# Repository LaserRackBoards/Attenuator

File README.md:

# Attenuator
Voltage Controlled Attenuator based on Mini-Circuits RVA-3000

* BNC connector for control voltage
* SMA connectors for RF-in and RF-out
* 10-turn potentiometer for set-point

Used for laser power stabilization via control of AOM rf drive power.

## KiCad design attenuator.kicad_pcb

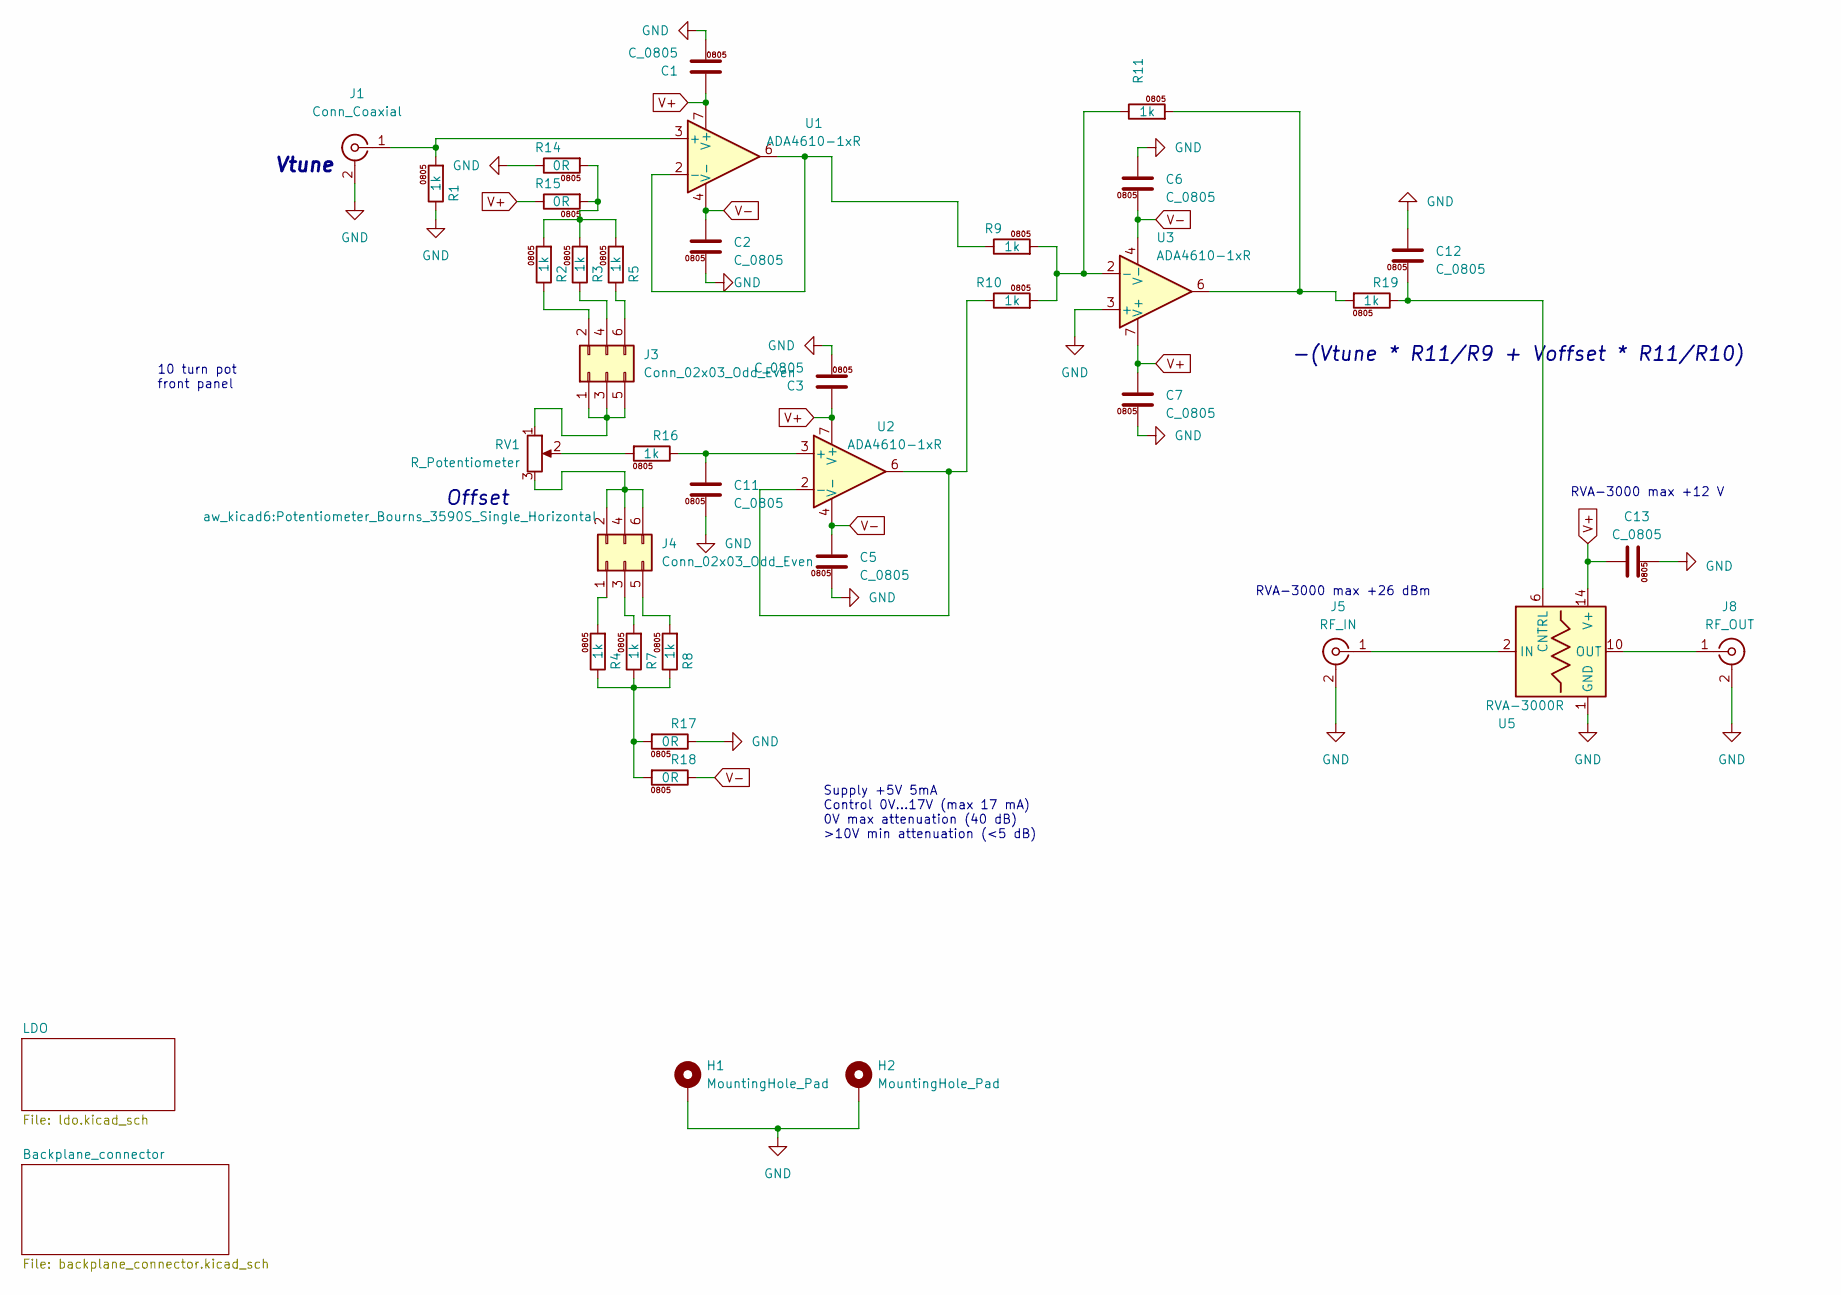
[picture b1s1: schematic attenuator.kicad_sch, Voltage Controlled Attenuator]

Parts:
C1, C2, C3, C5, C6, C7, C11, C12, C13: C_0805; C_0805_2012Metric
H1, H2: MountingHole_Pad; MountingHole_2.7mm_M2.5_DIN965_Pad
J1: Conn_Coaxial; BNC_Amphenol_B6252HB-NPP3G-50_Horizontal
J3, J4: Conn_02x03_Odd_Even; PinHeader_2x03_P2.54mm_Vertical
J5: RF_IN; SMA_Molex_73251-2200_Horizontal
J8: RF_OUT; SMA_Molex_73251-2200_Horizontal
R1, R2, R3, R4, R5, R7, R8, R9, R10, R11, R16, R19: 1k; R_0805_2012Metric
R14, R15, R17, R18: 0R; R_0805_2012Metric
RV1: R_Potentiometer; Potentiometer_Bourns_3590S_Single_Horizontal
U1, U2, U3: ADA4610-1xR; SOIC-8_3.9x4.9mm_P1.27mm
U5: RVA-3000R; Mini-Circuits_CK605

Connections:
GND: C1.2, C2.2, C3.2, C5.2, C6.1, C7.2, C11.2, C12.1, C13.2, H1.1, H2.1, J1.2 (Ext), J5.2 (Ext), J8.2 (Ext), R1.1, R14.1, R17.1, U3.3 (+), U5.1 (GND), U5.3 (GND), U5.4 (GND), U5.5 (GND), U5.7 (GND), U5.8 (GND), U5.9 (GND), U5.11 (GND), U5.12 (GND), U5.13 (GND), U5.15 (GND), U5.16 (GND); also elsewhere on the board
unnamed: J1.1 (In), R1.2, U1.3 (+)
unnamed: J3.1, J3.3, J3.5, RV1.1
unnamed: J3.2, R2.1
unnamed: J3.4, R3.1
unnamed: J3.6, R5.1
unnamed: J4.1, R4.2
unnamed: J4.2, J4.4, J4.6, RV1.3
unnamed: J4.3, R7.2
unnamed: J4.5, R8.2
unnamed: J5.1 (In), U5.2 (IN)
unnamed: J8.1 (In), U5.10 (OUT)
unnamed: R11.2, R19.2, U3.6
unnamed: R2.2, R3.2, R5.2, R14.2, R15.2
unnamed: R16.2, RV1.2
unnamed: R4.1, R7.1, R8.1, R17.2, R18.2
unnamed: R9.1, U1.2 (-), U1.6
unnamed: C11.1, R16.1, U2.3 (+)
unnamed: R10.1, U2.2 (-), U2.6
unnamed: R9.2, R10.2, R11.1, U3.2 (-)
unnamed: C12.2, R19.1, U5.6 (CNTRL)
V+: C1.1, C3.1, C7.1, C13.1, R15.1, U1.7 (V+), U2.7 (V+), U3.7 (V+), U5.14 (V+); also elsewhere on the board
V-: C2.1, C5.1, C6.2, R18.1, U1.4 (V-), U2.4 (V-), U3.4 (V-); also elsewhere on the board

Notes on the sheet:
RVA-3000 max +12 V
Supply +5V 5mA Control 0V...17V (max 17 mA) 0V max attenuation (40 dB) >10V min attenuation (<5 dB)
RVA-3000 max +26 dBm
Vtune
10 turn pot front panel
Offset
-(Vtune * R11/R9 + Voffset * R11/R10)

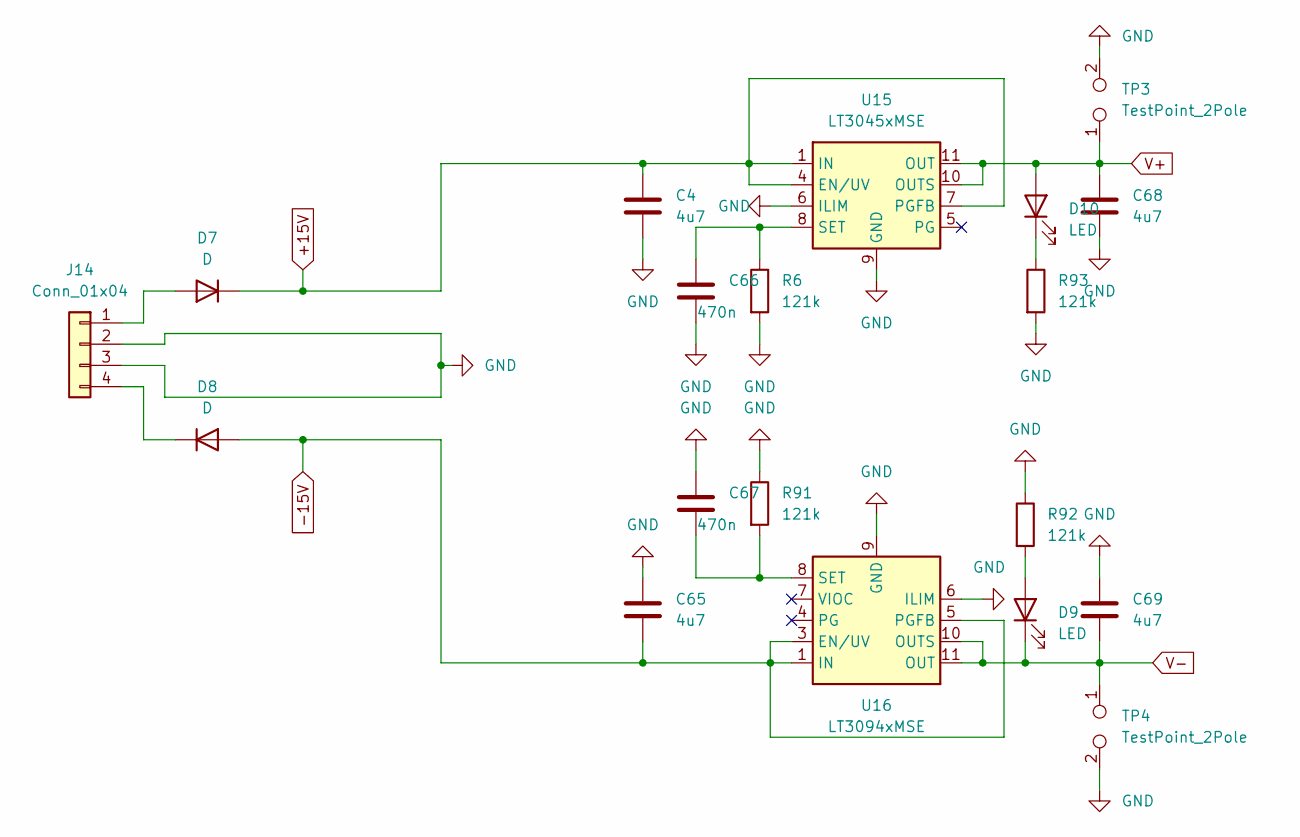
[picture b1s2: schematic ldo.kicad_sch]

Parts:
C4, C65, C68, C69: 4u7; C_0805_2012Metric
C66, C67: 470n; C_0805_2012Metric
D7, D8: D; D_SMB
D9, D10: LED; LED_0805_2012Metric
J14: Conn_01x04; TerminalBlock_TE_282834-4_1x04_P2.54mm_Horizontal
R6, R91, R92, R93: 121k; R_0805_2012Metric
TP3, TP4: TestPoint_2Pole; TestPoint_2Pads_Pitch2.54mm_Drill0.8mm
U15: LT3045xMSE; MSOP-12-1EP_3x4mm_P0.65mm_EP1.65x2.85mm
U16: LT3094xMSE; MSOP-12-1EP_3x4mm_P0.65mm_EP1.65x2.85mm

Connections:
+15V: C4.1, D7.1 (K), U15.1 (IN), U15.2 (IN), U15.3 (IN), U15.4 (EN/UV), U15.7 (PGFB); also elsewhere on the board
-15V: C65.2, D8.2 (A), U16.1 (IN), U16.2 (IN), U16.3 (EN/UV), U16.5 (PGFB), U16.13 (IN); also elsewhere on the board
GND: C4.2, C65.1, C66.2, C67.1, C68.2, C69.1, J14.2, J14.3, R6.2, R91.1, R92.1, R93.2, TP3.2, TP4.2, U15.6 (ILIM), U15.9 (GND), U15.13 (GND), U16.6 (ILIM), U16.9 (GND); also elsewhere on the board
unnamed: D7.2 (A), J14.1
unnamed: D8.1 (K), J14.4
unnamed: D9.2 (A), R92.2
unnamed: D10.1 (K), R93.1
unnamed: C66.1, R6.1, U15.8 (SET)
unnamed: C67.2, R91.2, U16.8 (SET)
V+: C68.1, D10.2 (A), TP3.1, U15.10 (OUTS), U15.11 (OUT), U15.12 (OUT); also elsewhere on the board
V-: C69.2, D9.1 (K), TP4.1, U16.10 (OUTS), U16.11 (OUT), U16.12 (OUT); also elsewhere on the board

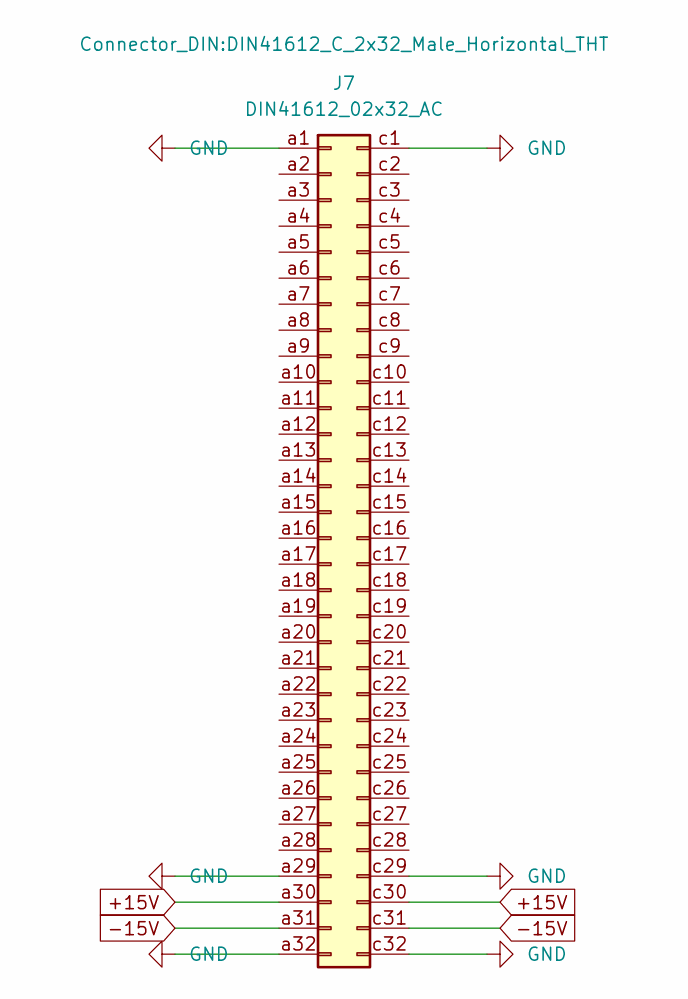
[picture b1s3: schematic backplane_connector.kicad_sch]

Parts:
J7: DIN41612_02x32_AC; DIN41612_C_2x32_Male_Horizontal_THT

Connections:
+15V: J7.a30, J7.c30; also elsewhere on the board
-15V: J7.a31, J7.c31; also elsewhere on the board
GND: J7.a1, J7.a29, J7.a32, J7.c1, J7.c29, J7.c32; also elsewhere on the board

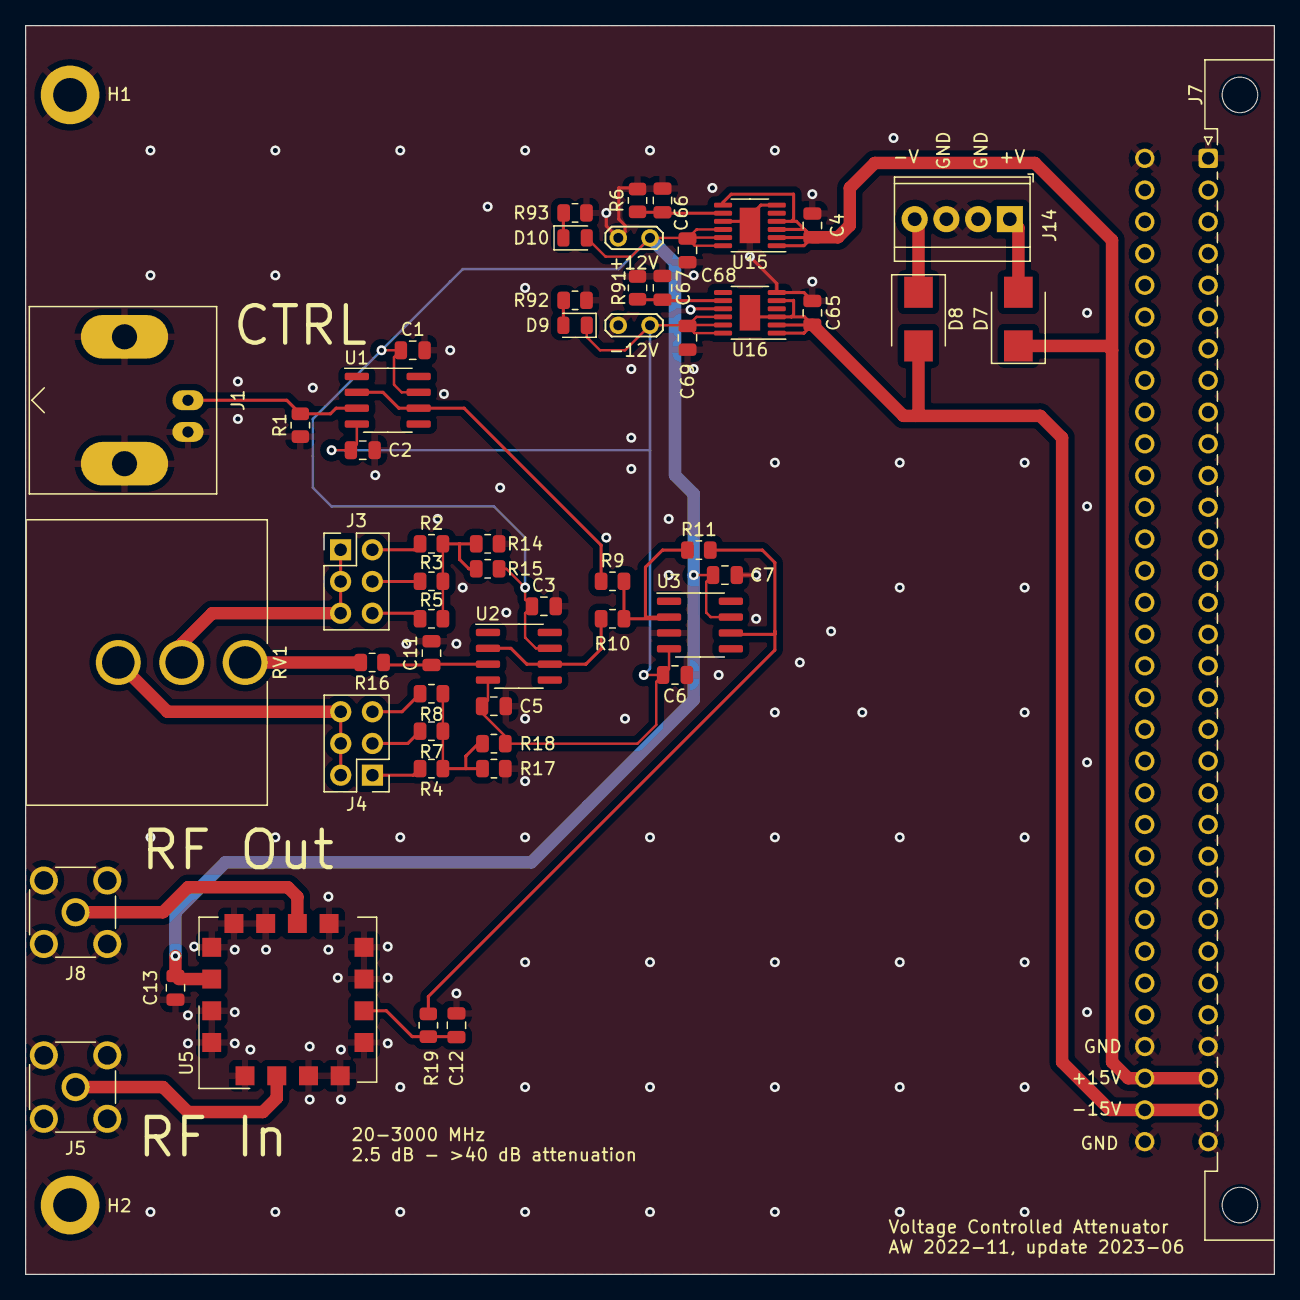
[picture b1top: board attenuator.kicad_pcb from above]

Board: 2 copper layers, 100.0 x 100.0 mm, 57 parts (0 on the bottom side), 31 nets.

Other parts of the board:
+12V: TestPoint_2Pole; TestPoint_2Pads_Pitch2.54mm_Drill0.8mm
-12V: TestPoint_2Pole; TestPoint_2Pads_Pitch2.54mm_Drill0.8mm

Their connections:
GND: +12V.2, -12V.2; also elsewhere on the board
V+: +12V.1; also elsewhere on the board
V-: -12V.1; also elsewhere on the board
